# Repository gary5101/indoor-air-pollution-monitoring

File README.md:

Motivation
==========

Food production areas are prone to much air pollution as they will be using inflammable fuels,burning coal and other organic matter.
Despite this pollution, these areas should be kept clear of other air pollutants and gases.

Overview
========

In this project we monitor the air pollutants(Particulates,Volatile Organic Compounds,Carbon monoxide,Nitrogen dioxide,Ammonia,Methane,Propane etc) in food production areas.

The data which is collected is then sent to cloud for easy monitoring and analytics.

Here we basically collect the amount of pollutants and check the levels to assure the safety of the workers and the standards of the food.

Importance
==========

<span>Need of our Project</span>

**AQI**

The AQI is an index for reporting daily air quality. It tells you how clean or polluted your air is, and what associated health effects might be a concern for you. EPA calculates the AQI for five major air pollutants regulated by the Clean Air Act: ground-level ozone, particle pollution (also known as particulate matter), carbon monoxide, sulfur dioxide, and nitrogen dioxide. EPA has established national air quality standards to protect public health .
We use our collected data and make a AQI value and compare to the above standards to ensure a healthy environment.

<span>AQI</span> The higher the AQI value, the greater the level of air pollution and the greater the health concern.

Description
===========

<span>Goals</span> 

**Goals**

-   Measure the air quality index in the messes

-   To upload the air quality index to the cloud regularly to ensure the safety levels are not crossed.

-   To analyze the data collected and provide a solution if the safety levels are breached

<span>Implementation</span> 

**Steps**

-   Making the layout of the circuit

-   Connecting the sensors and controller according to the circuit

-   Writing of the code to test the sensors

-   Building of a datbase in a cloud to store the data collected

-   Update the code to connect the microcontroller to the cloud

-   Designing the final structure of the node

-   Deployment of the device

-   Analyzing the data stored in the cloud

<span>Deployment</span>

At the time of deployment of the, each node contains:-

1.  All the sensors with board(enclosed)

2.  jio-fi

3.  powerbank(power supply)

In the end 4 such node are deployed i.e 2 node in each mess

-   NBH mess

-   North mess

<span>List of Sensors and Controllers</span>

-   NodeMCU

-   Nova PM2.5 - PM10 - High Precision Air Particulate Matter Sensor

-   Digital Temperature and Humidity Sensor

-   Grove multichannel gas sensor

-   Grove - VOC and eCO2 Gas Sensor

Tools and Technologies
======================

NodeMCU
=======

<span>NodeMCU</span>

NodeMCU is an open source LUA based firmware developed for ESP8266 wifi chip.The ESP8266 is a low-cost Wi-Fi chip developed by Espressif Systems with TCP/IP protocol. NodeMCU Dev Kit has Arduino like Analog (i.e. A0) and Digital (D0-D8) pins on its board.It supports serial communication protocols i.e. UART, SPI, I2C etc.

<span>NodeMCU Specifications</span> 

<span>NodeMCU vs esp32</span> ESP32 is more expensive than the ESP8266.Additionally, because it is more recent than the ESP8266, not all software has been developed to take the most out of the ESP32 functionalities, there is less support, and more bugs. But on the long run these issues will be fixed, and there will be space for both boards.

Nova PM2.5 - PM10 (SDS011)
==========================

<span>Nova PM2.5 - PM10 (SDS011)</span> The SDS011 using principle of laser scattering,can get the particle concentration between 0.3 to 10μm in the air. It gives direct digital output via serial protocol at 9600bps and also over 2 PWM channels. There is a built-in fan for stable and reliable operations. 

<span>Nova PM2.5 - PM10 (SDS011) Specifications</span> 

<span>Nova PM2.5 - PM10 (SDS011) Pin Layout</span>

-   Pin 1 - not connected

-   Pin 2 - PM2.5: 0-999μg/m³; PWM output

-   Pin 3 - 5V

-   Pin 4 - PM10: 0-999 μg/m³; PWM output

-   Pin 5 - GND

-   Pin 6 - RX UART (TTL) 3.3V

-   Pin 7 - TX UART (TTL) 3.3V

<span>SDS011 vs SPS30</span> 
SPS30 has sophisticated technology with high quality and long-lasting compounds which is used mostly for accurate measurements and which also makes it very expensive.For household environments SDS011 provides ease than SPS30.

DHT22 AM2302 Module
===================

<span>DHT22 AM2302 Module</span> It uses a capacitive humidity sensor and a thermistor to measure the surrounding air, and spits out a digital signal on the data pin (no analog input pins needed). Its fairly simple to use, but requires careful timing to grab data. The only real downside of this sensor is you can only get new data from it once every 2 seconds, so when using our library, sensor readings can be up to 2 seconds old. 

<span>DHT22 AM2302 Module Specifications</span>

-   Low cost

-   3 to 5V power and I/O

-   2.5mA max current use during conversion (while requesting data)

-   Good for 0-100

-   Good for -40 to 80$^circ$C temperature readings 0.5$^circ$C accuracy

-   No more than 0.5 Hz sampling rate (once every 2 seconds)

-   Body size 15.1mm x 25mm x 7.7mm

-   4 pins with 0.1" spacing

<span>DHT22 AM2302 Pin Layout</span> 

<span>DHT22 vs DHT11</span> The DHT22 is the more expensive version which obviously has better specifications. Its temperature measuring range is from -40 to +125 degrees Celsius with +-0.5 degrees accuracy, while the DHT11 temperature range is from 0 to 50 degrees Celsius with +-2 degrees accuracy. Also the DHT22 sensor has better humidity measuring range, from 0 to 100% with 2-5% accuracy, while the DHT11 humidity range is from 20 to 80% with 5% accuracy. 

Grove multichannel gas sensor
=============================

<span>Grove multichannel gas sensor</span> Grove Multichannel Gas sensor is a environment detecting sensor with a built in MiCS-6814 which can detect many unhealthful gases, and three gases can be measured simultaneously due to its multi channels, so it can help you to monitor the concentration which more than one gas. 

<span>Grove multichannel gas sensor (MICS 6814) Characteristics</span> 

<span>Grove multichannel gas sensor (MICS 6814) Specifications</span> **Features**

-   Three fully independent sensing elements on one package

-   Built with ATmega168PA

-   I2C interface with programmable address

-   Heating power can be shut down for low power

-   Detectable gases

-   Carbon monoxide CO 1 to 1000ppm

-   Nitrogen dioxide NO2 0.05 to 10ppm

-   Ethanol C2H6OH 10 to 500ppm

-   Hydrogen H2 1 to 1000ppm

-   Ammonia NH3 1 to 500ppm

-   Methane CH4 >1000ppm

-   Propane C3H8 >1000ppm

-   Iso-butane C4H10 >1000ppm

<span>Grove multichannel gas sensor (MICS 6814) Pin Layout</span> 

<span>MICS 6814 vs MICS 4514</span> 
MICS 4514 has CO/NO2 dual sensor whereas MICS 6814 has CO/NO2/NH3 triple sensor. The CO and NO2 measurements are taken by means of the MiCS-4514 MicroElectroMechanical Sensor (MEMS) [30]. This is a sensor typically used in automotive applications (e.g., to measure emissions from automobile exhausts). Hence, it is optimized for high concentration of gases,but in human environment where we don’t have such high concentrations, MICS 6814 works efficiently.

Grove - VOC and eCO2 Gas Sensor(SGP30)
======================================

<span>Grove - VOC and eCO2 Gas Sensor(SGP30)</span> The Grove-VOC and eCO2 Gas Sensor(SGP30) is an air quality detection sensor. This grove module is based on SGP30, provided TVOC(Total Volatile Organic Compounds) and CO2eq output for this module. 

<span>Grove - VOC and eCO2 Gas Sensor(SGP30) Specifications</span> 

<span>SGP30 Pin Layout</span> 

<span>SGP30 vs CCS811</span> 

From a firmware perspective SGP30 is almost as easy as the CCS811. From the test data, SGP30 is way more sensitive than the CCS811. If you are in an environment where you need to know SGP30 is the one to pick. SGP30 is widely available though many channels.

Technology
==========

<span>Technology</span> **Connecting to Cloud**
The program connects to the Wi-Fi network using the provided password and SSID. It then proceeds to connect to the provided cloud/host server , and sends the provided URI to the host server.
Once the data has been successfully sent, the sketch waits for a reply from the server. The process is repeated until the ESP8266 is turned off.

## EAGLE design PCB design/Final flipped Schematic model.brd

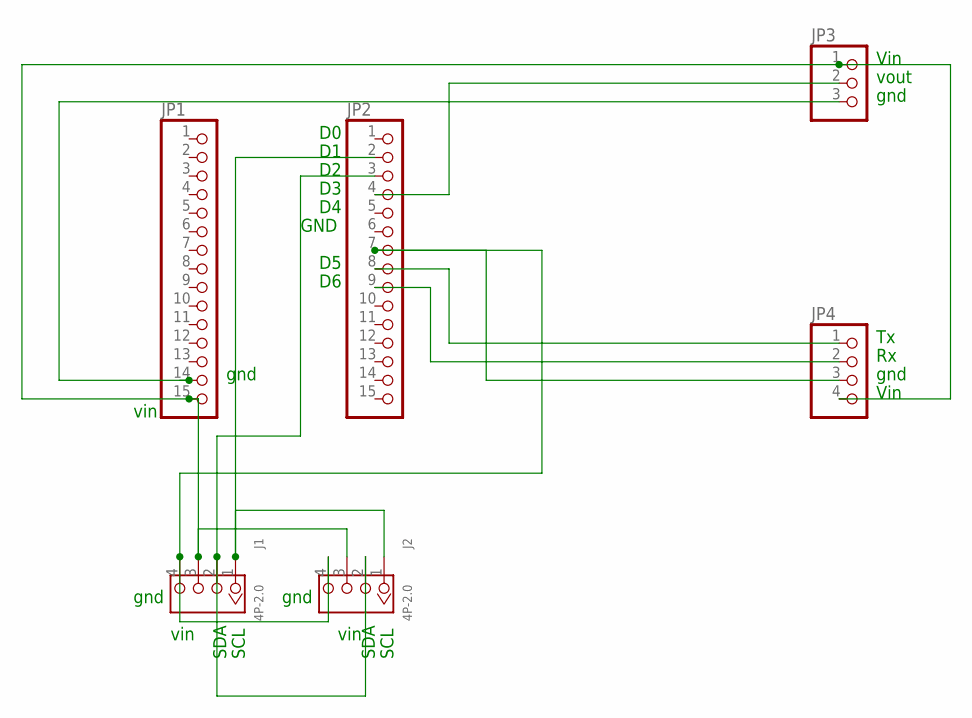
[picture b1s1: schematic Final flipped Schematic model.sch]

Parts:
J1, J2: 4P-2.0; HW4-2.0
JP1, JP2: PINHD-1X15; 1X15
JP3: PINHD-1X3; 1X03
JP4: PINHD-1X4; 1X04

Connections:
unnamed: JP2.8, JP4.1
unnamed: JP2.9, JP4.2
unnamed: JP2.4, JP3.2
unnamed: J1.1, J2.1, JP2.2
unnamed: J1.4, J2.4, JP2.7, JP4.3
unnamed: J1.2, J2.2, JP2.3
unnamed: J1.3, J2.3, JP1.15, JP3.1, JP4.4
unnamed: JP1.14, JP3.3

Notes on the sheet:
Vin
gnd
vout
GND
vin
SDA
SCL

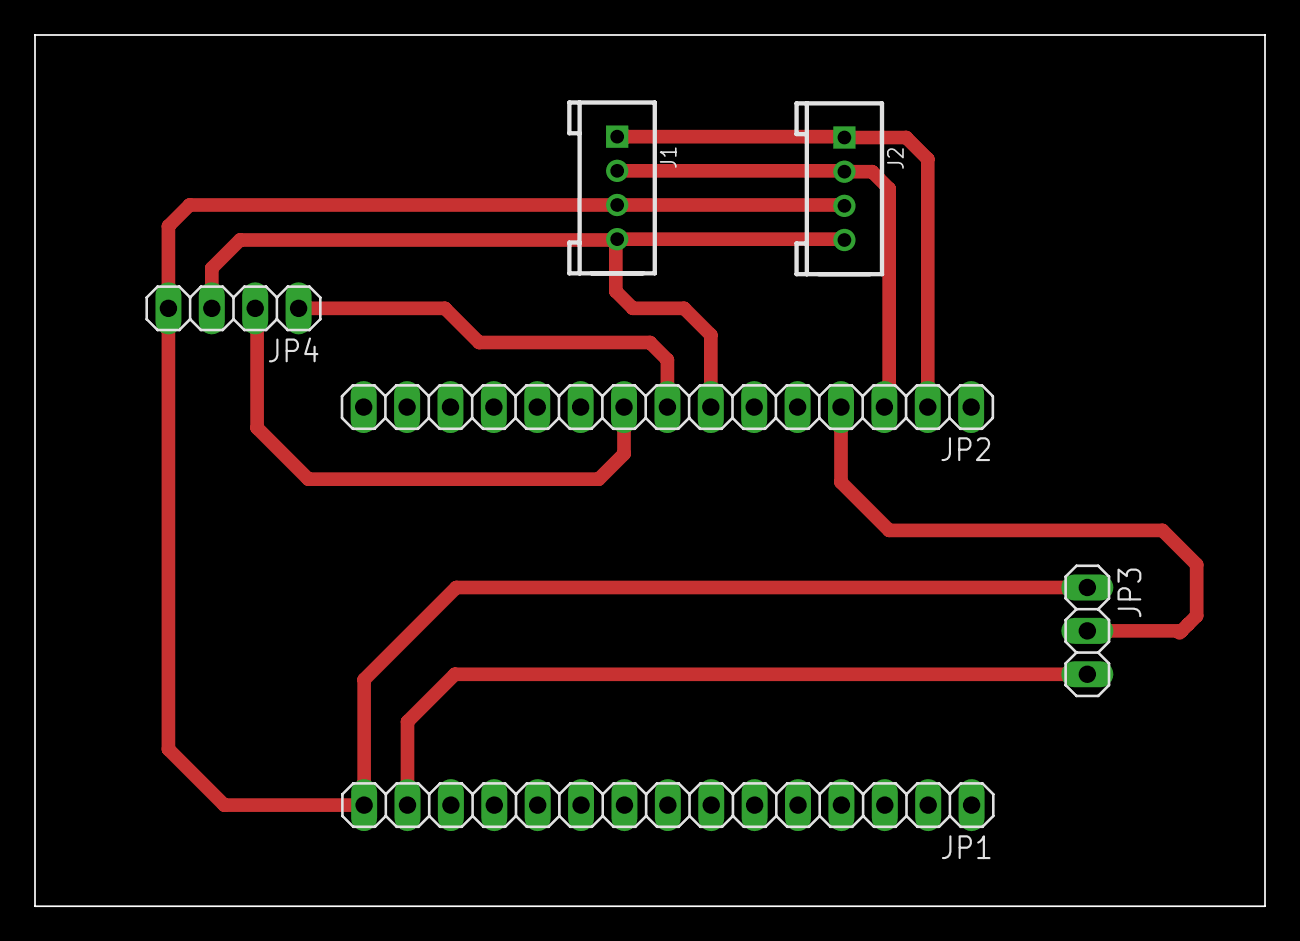
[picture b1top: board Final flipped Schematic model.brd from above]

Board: 2 copper layers, 72.0 x 51.0 mm, 6 parts (0 on the bottom side), 8 nets.

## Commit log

2019-12-08 final project
2019-12-08 documentation added
